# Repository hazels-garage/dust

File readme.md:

# dust
## ultrathin sweep-alike

| Left | Right |
| :---: | :---: |
|  |  |

**dust** is my attempt at making the thinnest sweep-alike.
### Sacrifices were made.  

- XIAO is surface mounted to be reversible without jumpers.  
- There is no reset button because the xiao has one on it.  
- Soldering the battery connection on the XIAO is gonna suck.
- You're probably gonna need to tape the battery to the board.

## MATERIALS
- 34x [Kailh X Switches](https://www.aliexpress.us/item/2251832799288171.html)
- 34x [1N4148 - SOD-123 Diodes](https://www.aliexpress.us/item/3256801606142520.html)
- 2x SeeedStudio XIAO (RP2040 or BLE)
- 2x [TRRS Jack](https://www.aliexpress.us/item/3256801742337046.html) (RP2040)
- 2x [Power Switch](https://mkultra.click/alps-ssss811101/) (BLE)
- 2x [Battery](https://tinycircuits.com/collections/all/products/lithium-ion-polymer-battery-3-7v-40mah) (BLE)
- 2x [Battery Connector](https://www.aliexpress.us/item/3256803789364982.html) (BLE)

## CASE
3D Printable case designed by ant: [Dust Tray](https://github.com/Ant6009/Dust_Tray)

## FIRMWARE

[QMK](https://github.com/jasonhazel/qmk_hazel/tree/master/keyboards/jasonhazel/dust)

[ZMK](https://github.com/jasonhazel/zmk-config/tree/master/config/boards/shields/dust)

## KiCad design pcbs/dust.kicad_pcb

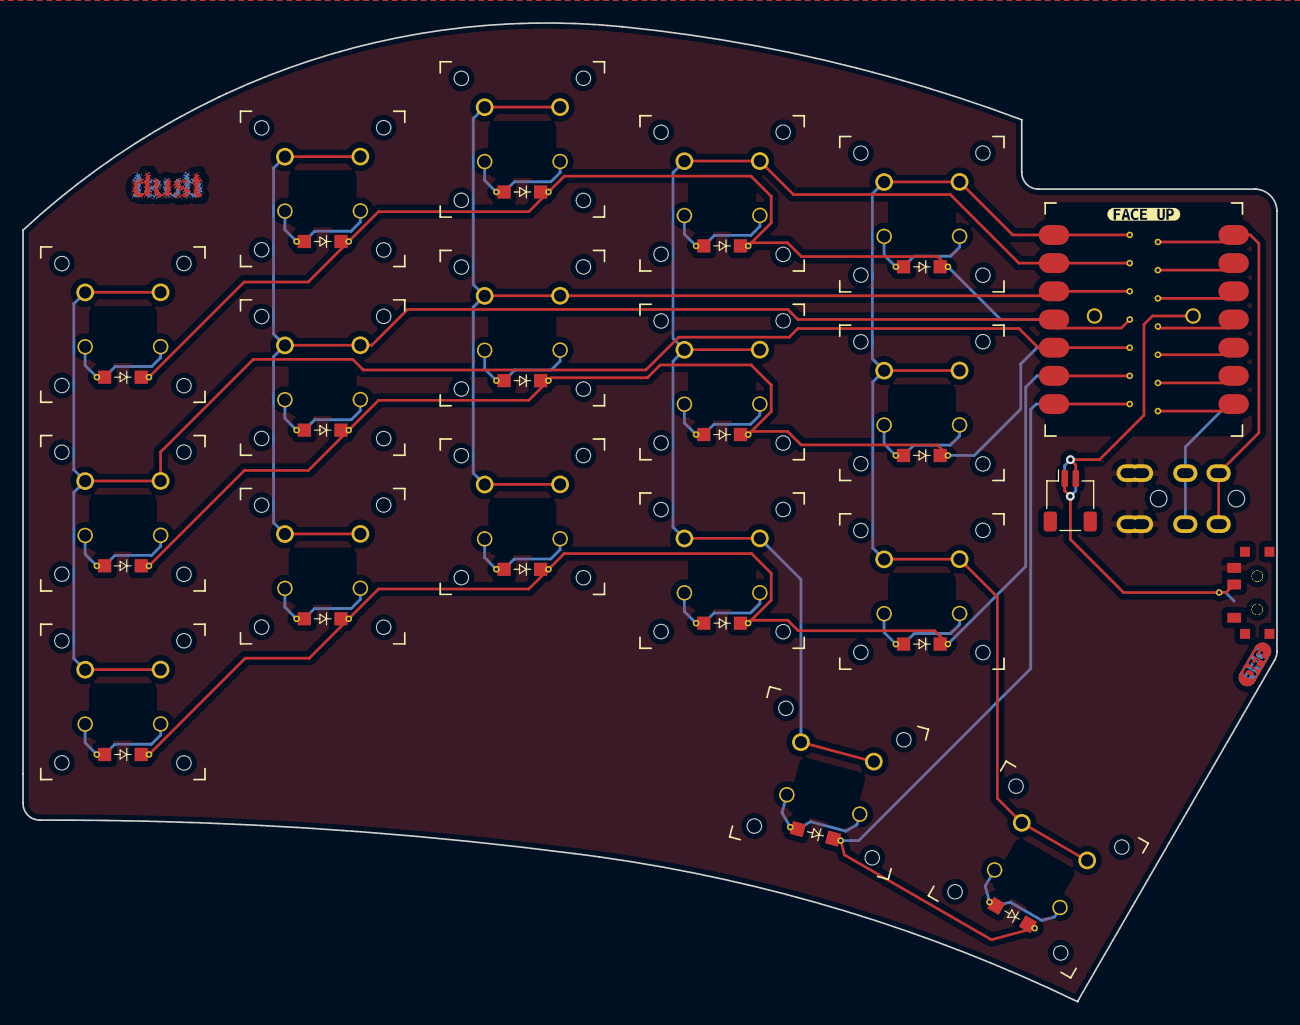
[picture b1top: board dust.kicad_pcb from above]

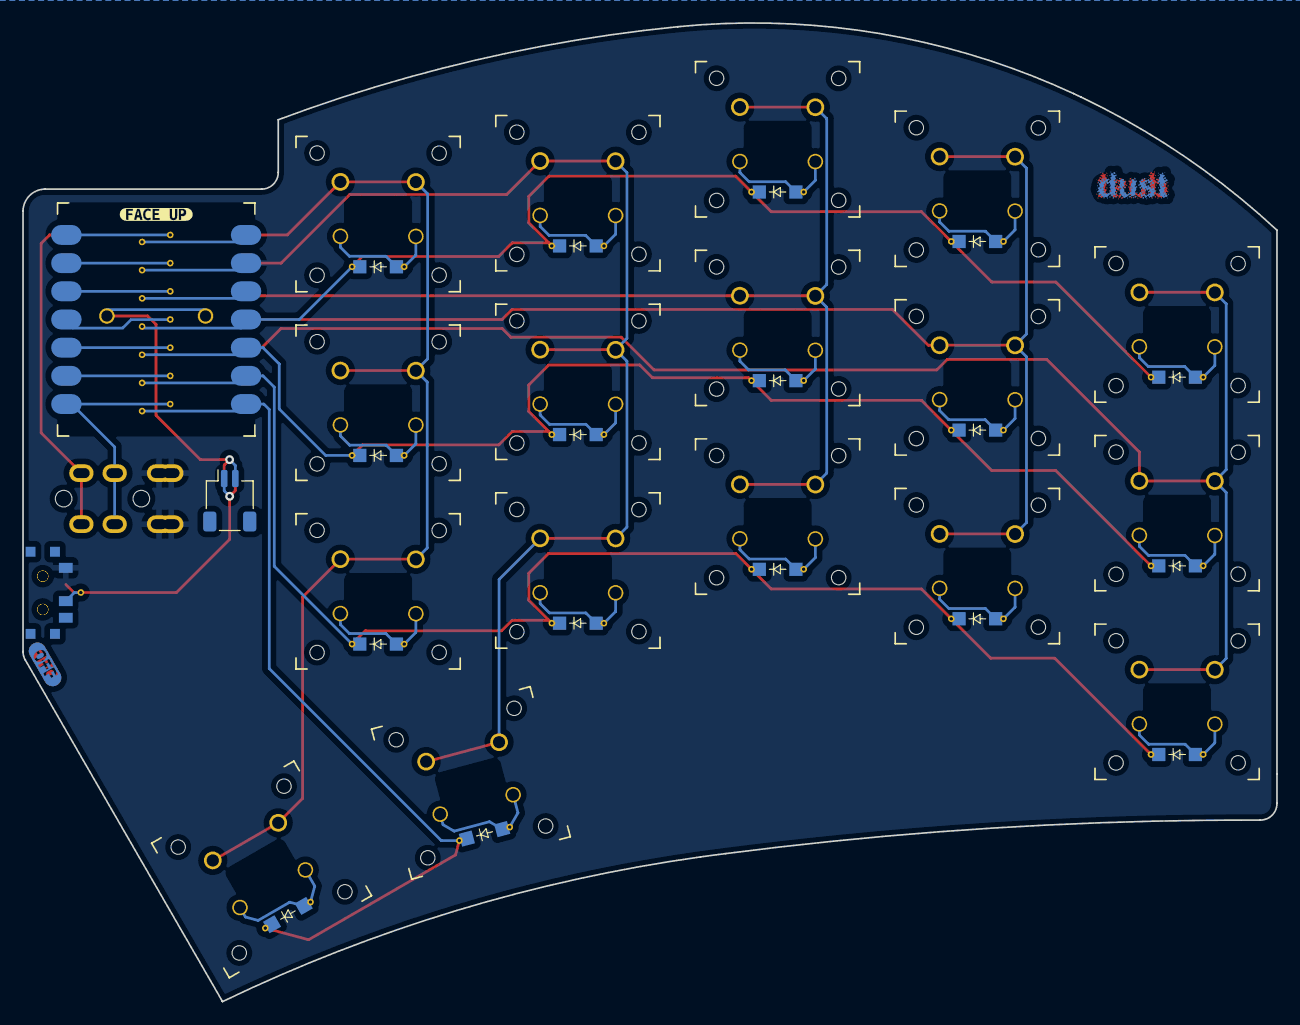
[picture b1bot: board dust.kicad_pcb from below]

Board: 2 copper layers, 113.0 x 88.2 mm, 43 parts (4 on the bottom side), 29 nets.

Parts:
BT2, BT2#2: Battery_Cell; JST_SH_SM02B-SRSS-TB_1x02-1MP_P1.00mm_Horizontal
D1, D2, D3, D4, D5, D6, D7, D8, D9, D10, D11, D12, D13, D14, D15, D16, D17: ComboDiode
S1, S2, S3, S4, S5, S6, S7, S8, S9, S10, S11, S12, S13, S14, S15, S16, S17: Kailh-PG1425-X-Switch-revers
T1, T1#2: SPDT_C128955
XIAO1: xiao-rev
kibuzzard-637F21E7, kibuzzard-637F21E7#2: G***; kibuzzard-637F21E7
kibuzzard-6383179D, kibuzzard-6383179D#2: G***; kibuzzard-6383179D

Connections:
BAT: BT2.2, BT2#2.2, XIAO1.19
BAT-: BT2.1, BT2#2.1, T1.2, T1#2.2
GND: T1.3, T1#2.1, XIAO1.13
c0: S1.1, S2.1, S3.1, XIAO1.5
c1: S4.1, S5.1, S6.1, XIAO1.4
c2: S7.1, S8.1, S9.1, XIAO1.3
c3: S10.1, S11.1, S12.1, S17.1, XIAO1.2
c4: S13.1, S14.1, S15.1, S16.1, XIAO1.1
index_bottom: D10.2, S10.2
index_home: D11.2, S11.2
index_top: D12.2, S12.2
inner_bottom: D13.2, S13.2
inner_home: D14.2, S14.2
inner_top: D15.2, S15.2
middle_bottom: D7.2, S7.2
middle_home: D8.2, S8.2
middle_thumb: D17.2, S17.2
middle_top: D9.2, S9.2
pinky_bottom: D1.2, S1.2
pinky_home: D2.2, S2.2
pinky_top: D3.2, S3.2
r0: D16.1, D17.1, XIAO1.8
r1: D1.1, D4.1, D7.1, D10.1, D13.1, XIAO1.9
r2: D2.1, D5.1, D8.1, D11.1, D14.1, XIAO1.10
r3: D3.1, D6.1, D9.1, D12.1, D15.1, XIAO1.11
right_thumb: D16.2, S16.2
ring_bottom: D4.2, S4.2
ring_home: D5.2, S5.2
ring_top: D6.2, S6.2

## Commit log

2022-11-24 init
2022-11-24 keep
2022-11-24 Update gallery (automated)
2022-11-24 update render path
2022-11-24 more notes
2022-11-24 more warnings
2022-12-06 slight changes to pcb
2022-12-06 remove untested from readme
2023-03-02 case link
    added link to case from ant.

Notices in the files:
readme.md:
https://img.shields.io/github/license/hazels-garage/dust?label=%20&logo=creativecommons&logoColor=%23ffffff&style=flat-square
